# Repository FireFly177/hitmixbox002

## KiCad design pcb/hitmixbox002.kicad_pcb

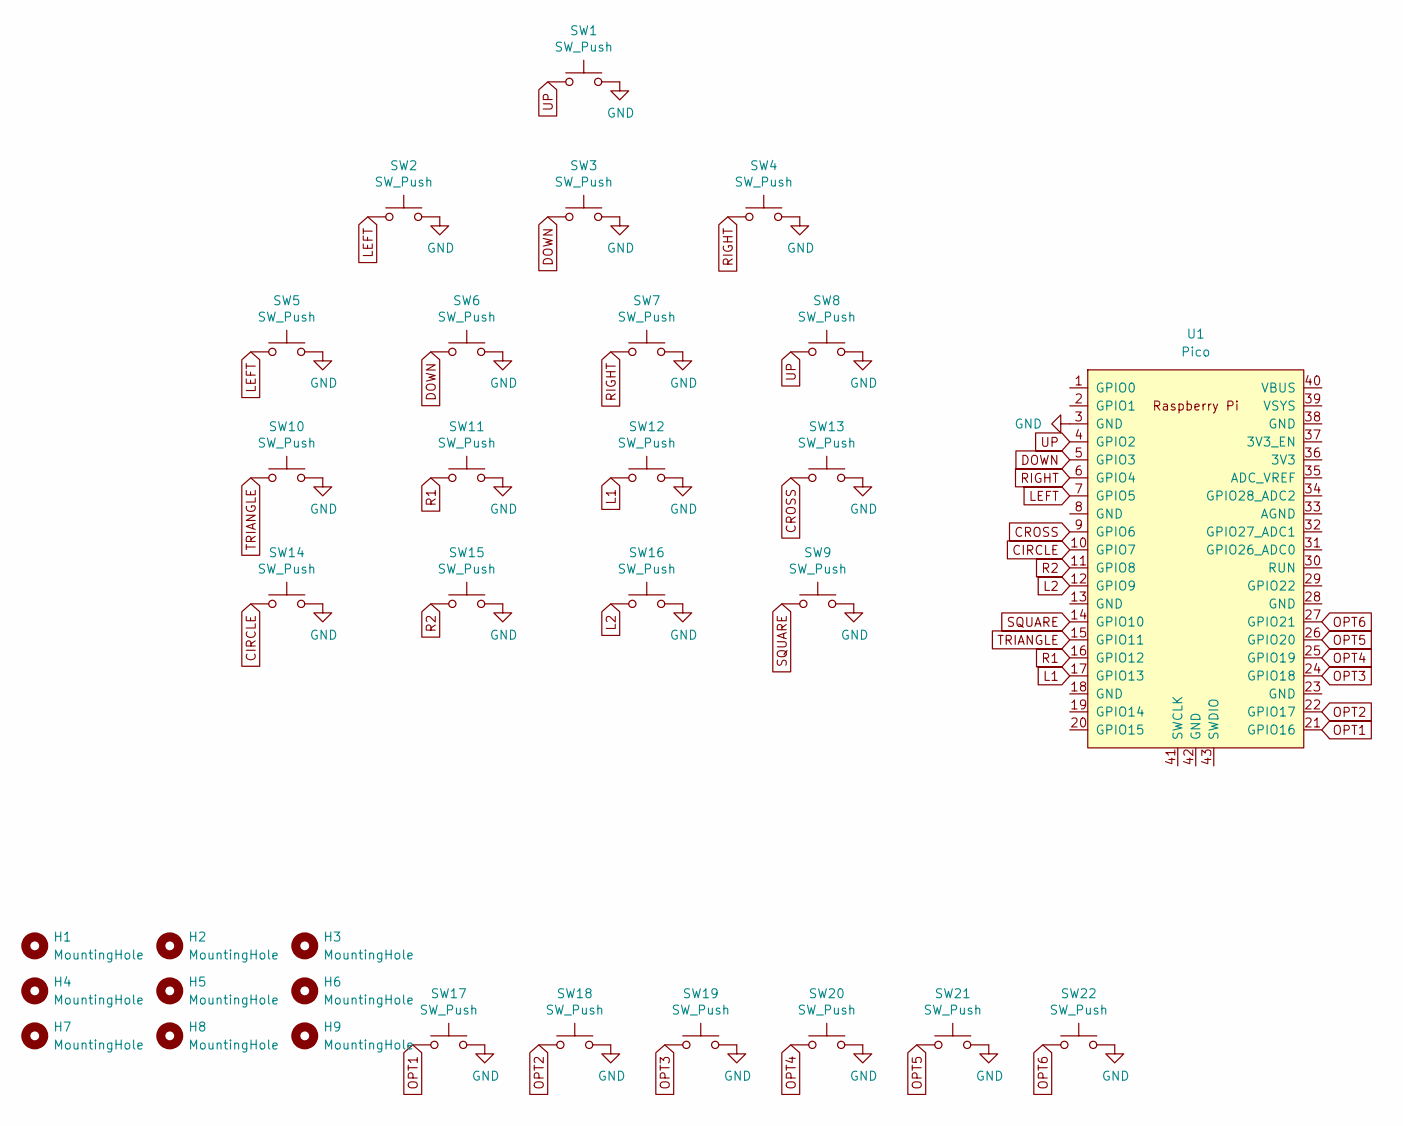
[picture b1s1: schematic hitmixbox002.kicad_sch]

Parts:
H1, H2, H3, H4, H5, H6, H7, H8, H9: MountingHole; MountingHole_6.4mm_M6
SW1, SW2, SW3, SW4, SW5, SW6, SW7, SW8, SW9, SW10, SW11, SW12, SW13, SW14, SW15, SW16: SW_Push; CherryMX_Choc_Hotswap
SW17, SW18, SW19, SW20, SW21, SW22: SW_Push; SW_PUSH_6mm_H5mm
U1: Pico; RPi_Pico_SMD_TH

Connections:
CIRCLE: SW14.1, U1.10 (GPIO7)
CROSS: SW13.1, U1.9 (GPIO6)
DOWN: SW3.1, SW6.1, U1.5 (GPIO3)
GND: SW1.2, SW2.2, SW3.2, SW4.2, SW5.2, SW6.2, SW7.2, SW8.2, SW9.2, SW10.2, SW11.2, SW12.2, SW13.2, SW14.2, SW15.2, SW16.2, SW17.2, SW18.2, SW19.2, SW20.2, SW21.2, SW22.2, U1.3 (GND)
L1: SW12.1, U1.17 (GPIO13)
L2: SW16.1, U1.12 (GPIO9)
LEFT: SW2.1, SW5.1, U1.7 (GPIO5)
OPT1: SW17.1, U1.21 (GPIO16)
OPT2: SW18.1, U1.22 (GPIO17)
OPT3: SW19.1, U1.24 (GPIO18)
OPT4: SW20.1, U1.25 (GPIO19)
OPT5: SW21.1, U1.26 (GPIO20)
OPT6: SW22.1, U1.27 (GPIO21)
R1: SW11.1, U1.16 (GPIO12)
R2: SW15.1, U1.11 (GPIO8)
RIGHT: SW4.1, SW7.1, U1.6 (GPIO4)
SQUARE: SW9.1, U1.14 (GPIO10)
TRIANGLE: SW10.1, U1.15 (GPIO11)
UP: SW1.1, SW8.1, U1.4 (GPIO2)

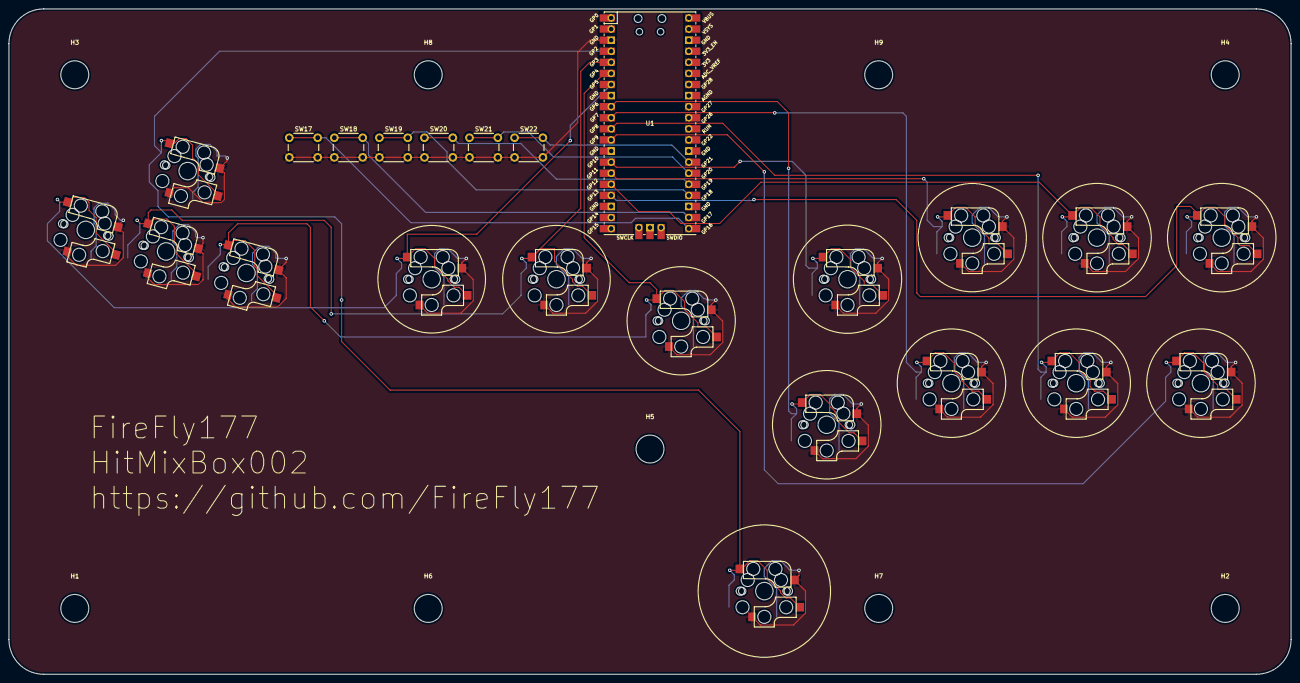
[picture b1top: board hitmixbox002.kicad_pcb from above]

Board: 2 copper layers, 293.7 x 152.4 mm, 32 parts (0 on the bottom side), 19 nets.

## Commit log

2023-05-31 clean up pcb folder
